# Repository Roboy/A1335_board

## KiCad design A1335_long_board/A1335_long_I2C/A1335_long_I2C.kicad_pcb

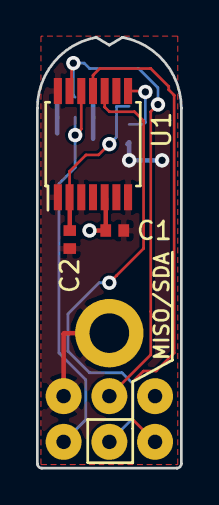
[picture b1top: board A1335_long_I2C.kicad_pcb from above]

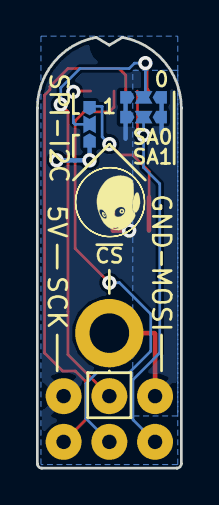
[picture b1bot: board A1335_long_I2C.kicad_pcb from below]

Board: 2 copper layers, 8.0 x 23.9 mm, 13 parts (4 on the bottom side), 8 nets.

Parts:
5V: 5V; SolderWirePad_1x01_Drill0.8mm
C1, C2: 100n; The_0402_FP
GND: GND; SolderWirePad_1x01_Drill0.8mm
H1: MountingHole_Pad; MountingHole_2.2mm_M2_DIN965_Pad
MISO/SDA: SDA/MISO; SolderWirePad_1x01_Drill0.8mm
MOSI: MOSI; SolderWirePad_1x01_Drill0.8mm
SA0: SA0; Solder_Bridge_3_0402
SA1: SA1; Solder_Bridge_3_0402
SCK: SCL/K; SolderWirePad_1x01_Drill0.8mm
SPI-I2C: I2C/SPI; Solder_Bridge_3_0402
U1: A1335LLETR-T; TSSOP-14_4.4x5mm_P0.65mm
svg2mod: G***; Roboy_Logo_F.SilkS

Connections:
+5V: 5V.1, C1.2, SA0.1, SA1.1, U1.5
/BYP: C2.1, SPI-I2C.1, U1.2
/SA0_~CS: SA0.2, U1.13
/SA1_MOSI: MOSI.1, SA1.2, U1.12
/SCL_SCLK: SCK.1, U1.11
/SDA_MISO: MISO/SDA.1, U1.10
GND: C1.1, C2.2, GND.1, H1.1, SA0.3, SA1.3, SPI-I2C.3, U1.1, U1.3, U1.7, U1.14
unnamed: SPI-I2C.2, U1.8

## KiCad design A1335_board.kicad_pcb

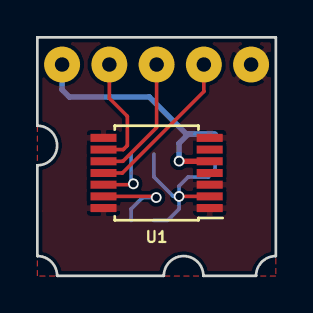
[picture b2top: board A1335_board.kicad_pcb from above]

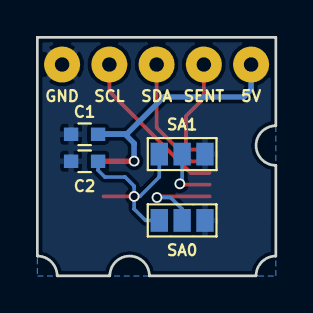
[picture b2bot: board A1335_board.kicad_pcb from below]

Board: 2 copper layers, 13.2 x 13.2 mm, 10 parts (9 on the bottom side), 8 nets.

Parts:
5V: 5V; SolderWirePad_single_0-8mmDrill
C1, C2: 100n; C_0603
GND: GND; SolderWirePad_single_0-8mmDrill
SA0, SA1: GS3
SCL: SCL; SolderWirePad_single_0-8mmDrill
SDA: SDA; SolderWirePad_single_0-8mmDrill
SENT: SENT; SolderWirePad_single_0-8mmDrill
U1: Generic_TSSOP-14; TSSOP-14_4.4x5mm_Pitch0.65mm

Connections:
+5V: 5V.1, C1.1, U1.5
GND: C1.2, C2.2, GND.1, SA0.1, SA1.1, U1.1, U1.3, U1.7, U1.8, U1.14
unnamed: C2.1, SA0.3, SA1.3, U1.2
unnamed: SDA.1, U1.10
unnamed: SCL.1, U1.11
unnamed: SENT.1, U1.9
unnamed: SA0.2, U1.13
unnamed: SA1.2, U1.12

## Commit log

2017-06-21 Initial commit: Board for a magnetic angle sensor with TSSOP-14 packaging. Rough placement of components for a start, and 3D STEP export
2017-06-22 minor re-export to step
2017-06-25 Finished routing and layout, and edited the schematic to include two solder bridges to select the device address. Also added two M2 mounting holes on the bottom.
2017-06-27 Added mounting holes (M2)
2017-06-27 Minor outline fix: Bottom line segment was on y pos 111mm instead of 111,01mm.
2017-06-28 Yet another minor outline fix: topmost left outline segment started on y=9something.76 instead of 9x.75
2017-06-28 I was fooled by the grid! My board was offset 0.01mm from the grid, wtf? Removed previous corrections and adjusted board outline to match the 0.125mm grid
2017-07-06 Reexported the 3D model
2017-07-11 Exported gerbers and drill files. Zip file is ready for production babygit add .
2019-01-22 Changed folder structure to add the second variant of the sensor board. Square board still the original; long version already with address and mode selection (I2C/SPI, despite the name only saying I2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
2020-03-12 2x6 panel
2020-03-12 hm weirdly displayed in pcbway gerberviewer, lets see...
2020-03-16 mouse bite bigger distances
2020-03-17 fixed create array
2020-06-21 with step export
